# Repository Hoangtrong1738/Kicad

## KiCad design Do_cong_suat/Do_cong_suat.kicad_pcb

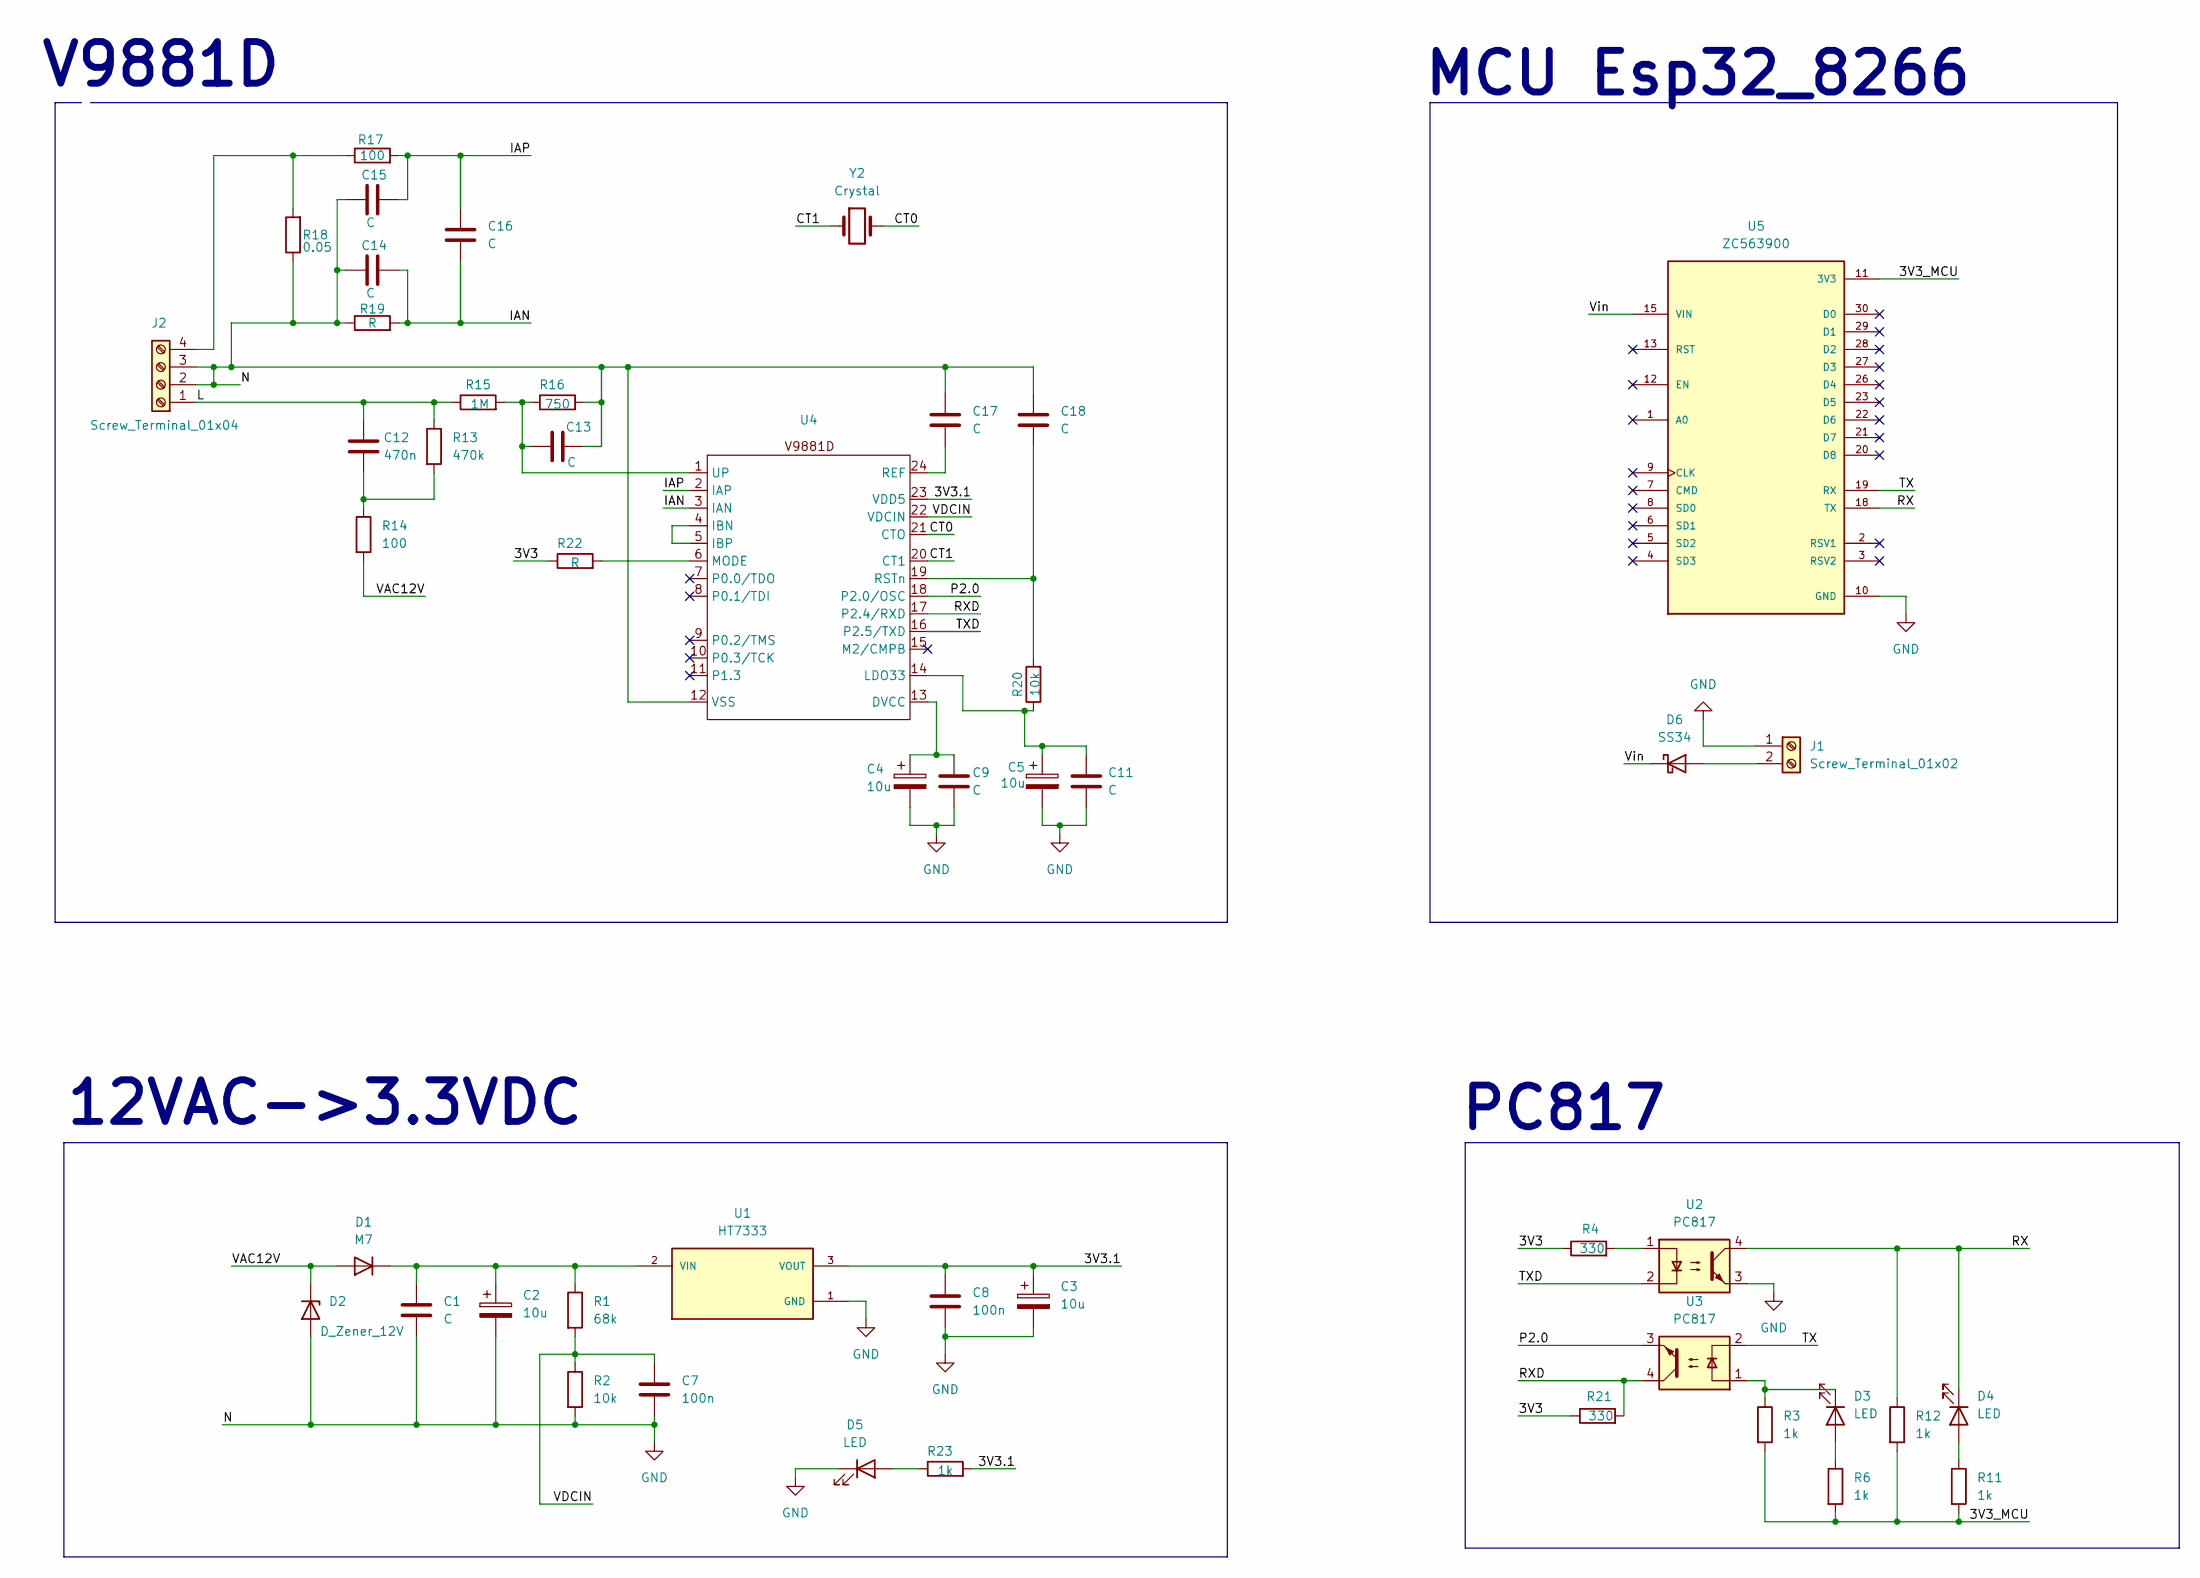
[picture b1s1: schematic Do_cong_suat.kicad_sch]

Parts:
C1, C9, C11, C13, C14, C15, C16, C17, C18: C; C_0805_2012Metric
C2: 10u; CP_Elec_5x5.4
C3, C4, C5: 10u; CP_EIA-3528-12_Kemet-T_HandSolder
C7, C8: 100n; C_0805_2012Metric
C12: 470n; C_Rect_L31.5mm_W15.0mm_P27.50mm_MKS4
D1: M7; D_SMA
D2: D_Zener_12V; D_SMA
D3, D4, D5: LED; LED_0805_2012Metric
D6: SS34; D_SMA
J1: Screw_Terminal_01x02; TerminalBlock_Phoenix_MKDS-1,5-2-5.08_1x02_P5.08mm_Horizont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
J2: Screw_Terminal_01x04; TerminalBlock_Phoenix_MKDS-1,5-4-5.08_1x04_P5.08mm_Horizont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
R1: 68k; R_0805_2012Metric
R2, R20: 10k; R_0805_2012Metric
R3, R6, R11, R12, R23: 1k; R_0805_2012Metric
R4, R21: 330; R_0805_2012Metric
R13: 470k; R_Axial_DIN0309_L9.0mm_D3.2mm_P15.24mm_Horizontal
R14, R17: 100; R_0805_2012Metric
R15: 1M; R_Axial_DIN0207_L6.3mm_D2.5mm_P10.16mm_Horizontal
R16: 750; R_0805_2012Metric
R18: 0.05; R_0805_2012Metric
R19, R22: R; R_0805_2012Metric
U1: HT7333; IC_HT7333; PARTREV 1.80
U2, U3: PC817; DIP-4_W7.62mm
U4: V9881D
U5: ZC563900; MODULE_ZC563900; PARTREV 1.0
Y2: Crystal; Crystal_AT310_D3.0mm_L10.0mm_Horizontal_1EP_style1

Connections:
/3V3.1: C3.1, C8.1, R23.2, U1.3 (VOUT), U4.23 (VDD5)
/CT0: U4.21 (CTO), Y2.2
/CT1: U4.20 (CT1), Y2.1
/IAN: C14.2, C16.2, R19.2, U4.3 (IAN)
/IAP: C15.2, C16.1, R17.2, U4.2 (IAP)
/L: C12.1, J2.1, R13.1, R15.1
/P2.0: U3.3, U4.18 (P2.0/OSC)
/RX: D4.1 (K), R12.1, U2.4, U5.18 (TX)
/RXD: R21.2, U3.4, U4.17 (P2.4/RXD)
/TX: U3.2, U5.19 (RX)
/TXD: U2.2, U4.16 (P2.5/TXD)
/VAC12V: D1.2 (A), D2.1 (K), R14.2
/VDCIN: C7.1, R1.2, R2.1, U4.22 (VDCIN)
/Vin: D6.1 (K), U5.15 (VIN)
GND: C1.2, C2.2, C3.2, C4.2, C5.2, C7.2, C8.2, C9.2, C11.2, C13.2, C14.1, C15.1, C17.1, C18.1, D2.2 (A), D5.1 (K), J1.1, J2.2, J2.3, R2.2, R16.2, R18.1, R19.1, U1.1 (GND), U2.3, U4.12 (VSS), U5.10 (GND), U5.14 (GND), U5.17 (GND), U5.24 (GND)
unnamed: C12.2, R13.2, R14.1
unnamed: C1.1, C2.1, D1.1 (K), R1.1, U1.2 (VIN)
unnamed: D3.2 (A), R6.1
unnamed: D3.1 (K), R3.1, U3.1
unnamed: D4.2 (A), R11.1
unnamed: D5.2 (A), R23.1
unnamed: D6.2 (A), J1.2
unnamed: J2.4, R17.1, R18.2
unnamed: R4.2, U2.1
unnamed: C4.1, C9.1, U4.13 (DVCC)
unnamed: U4.4 (IBN), U4.5 (IBP)
unnamed: C5.1, C11.1, R20.1, U4.14 (LDO33)
unnamed: R22.2, U4.6 (MODE)
unnamed: C17.2, U4.24 (REF)
unnamed: C18.2, R20.2, U4.19 (RSTn)
unnamed: C13.1, R15.2, R16.1, U4.1 (UP)

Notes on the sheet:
12VAC->3.3VDC
PC817
MCU Esp32_8266
V9881D

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
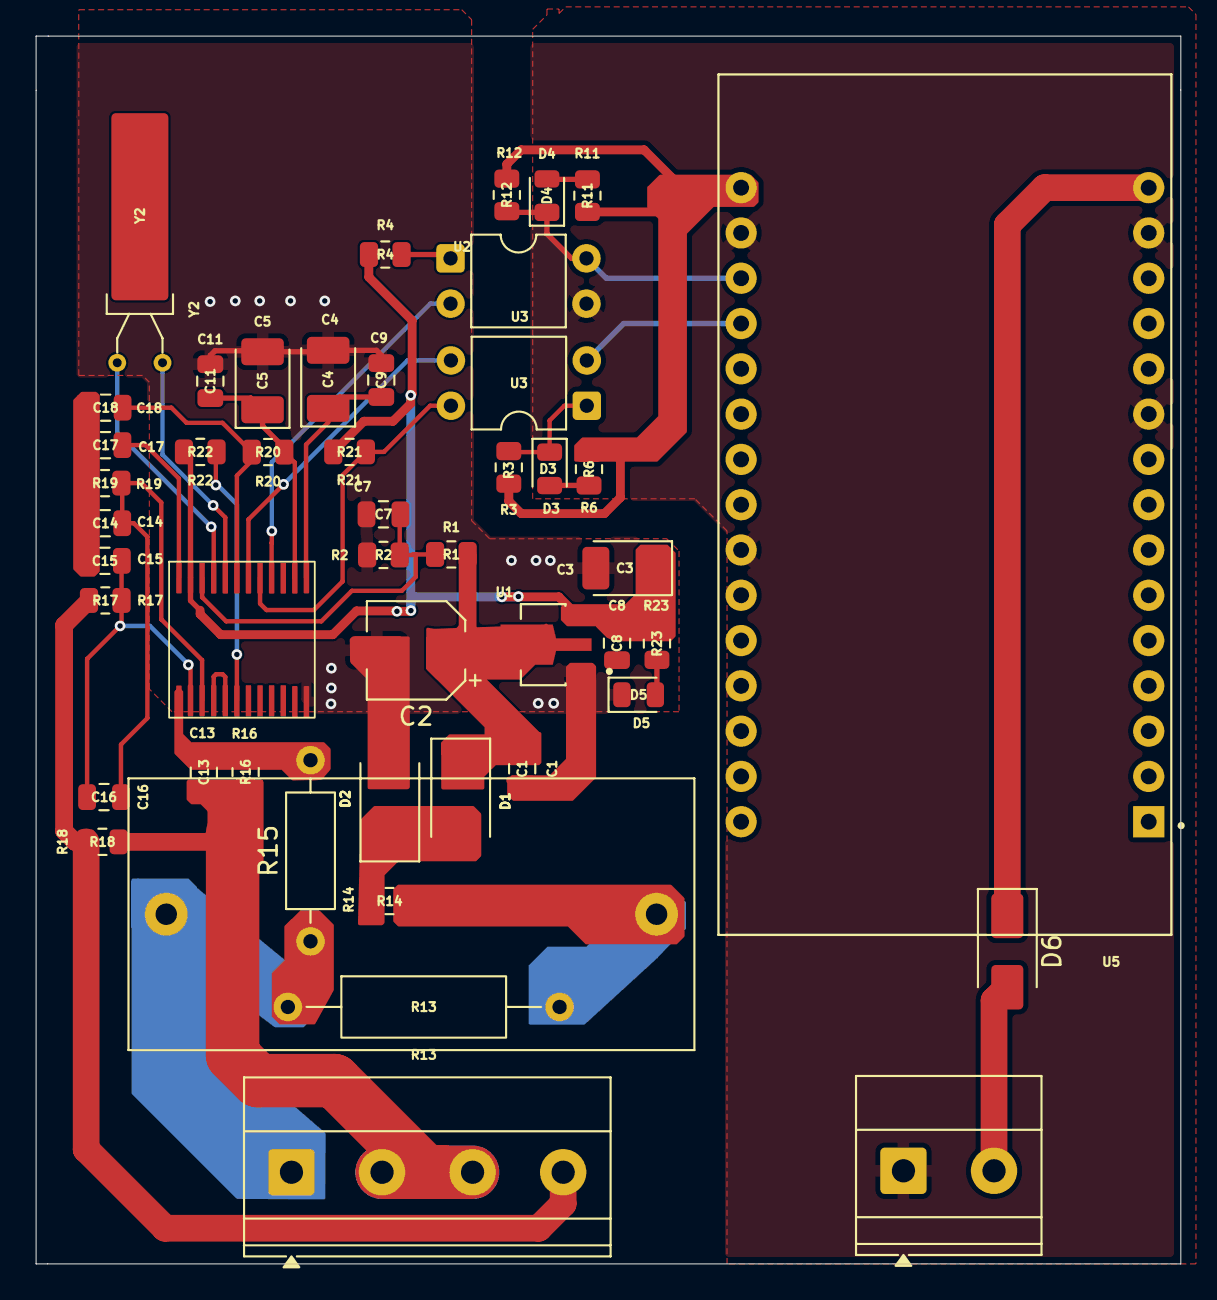
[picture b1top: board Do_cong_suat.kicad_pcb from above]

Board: 2 copper layers, 64.2 x 68.9 mm, 48 parts (0 on the bottom side), 32 nets.

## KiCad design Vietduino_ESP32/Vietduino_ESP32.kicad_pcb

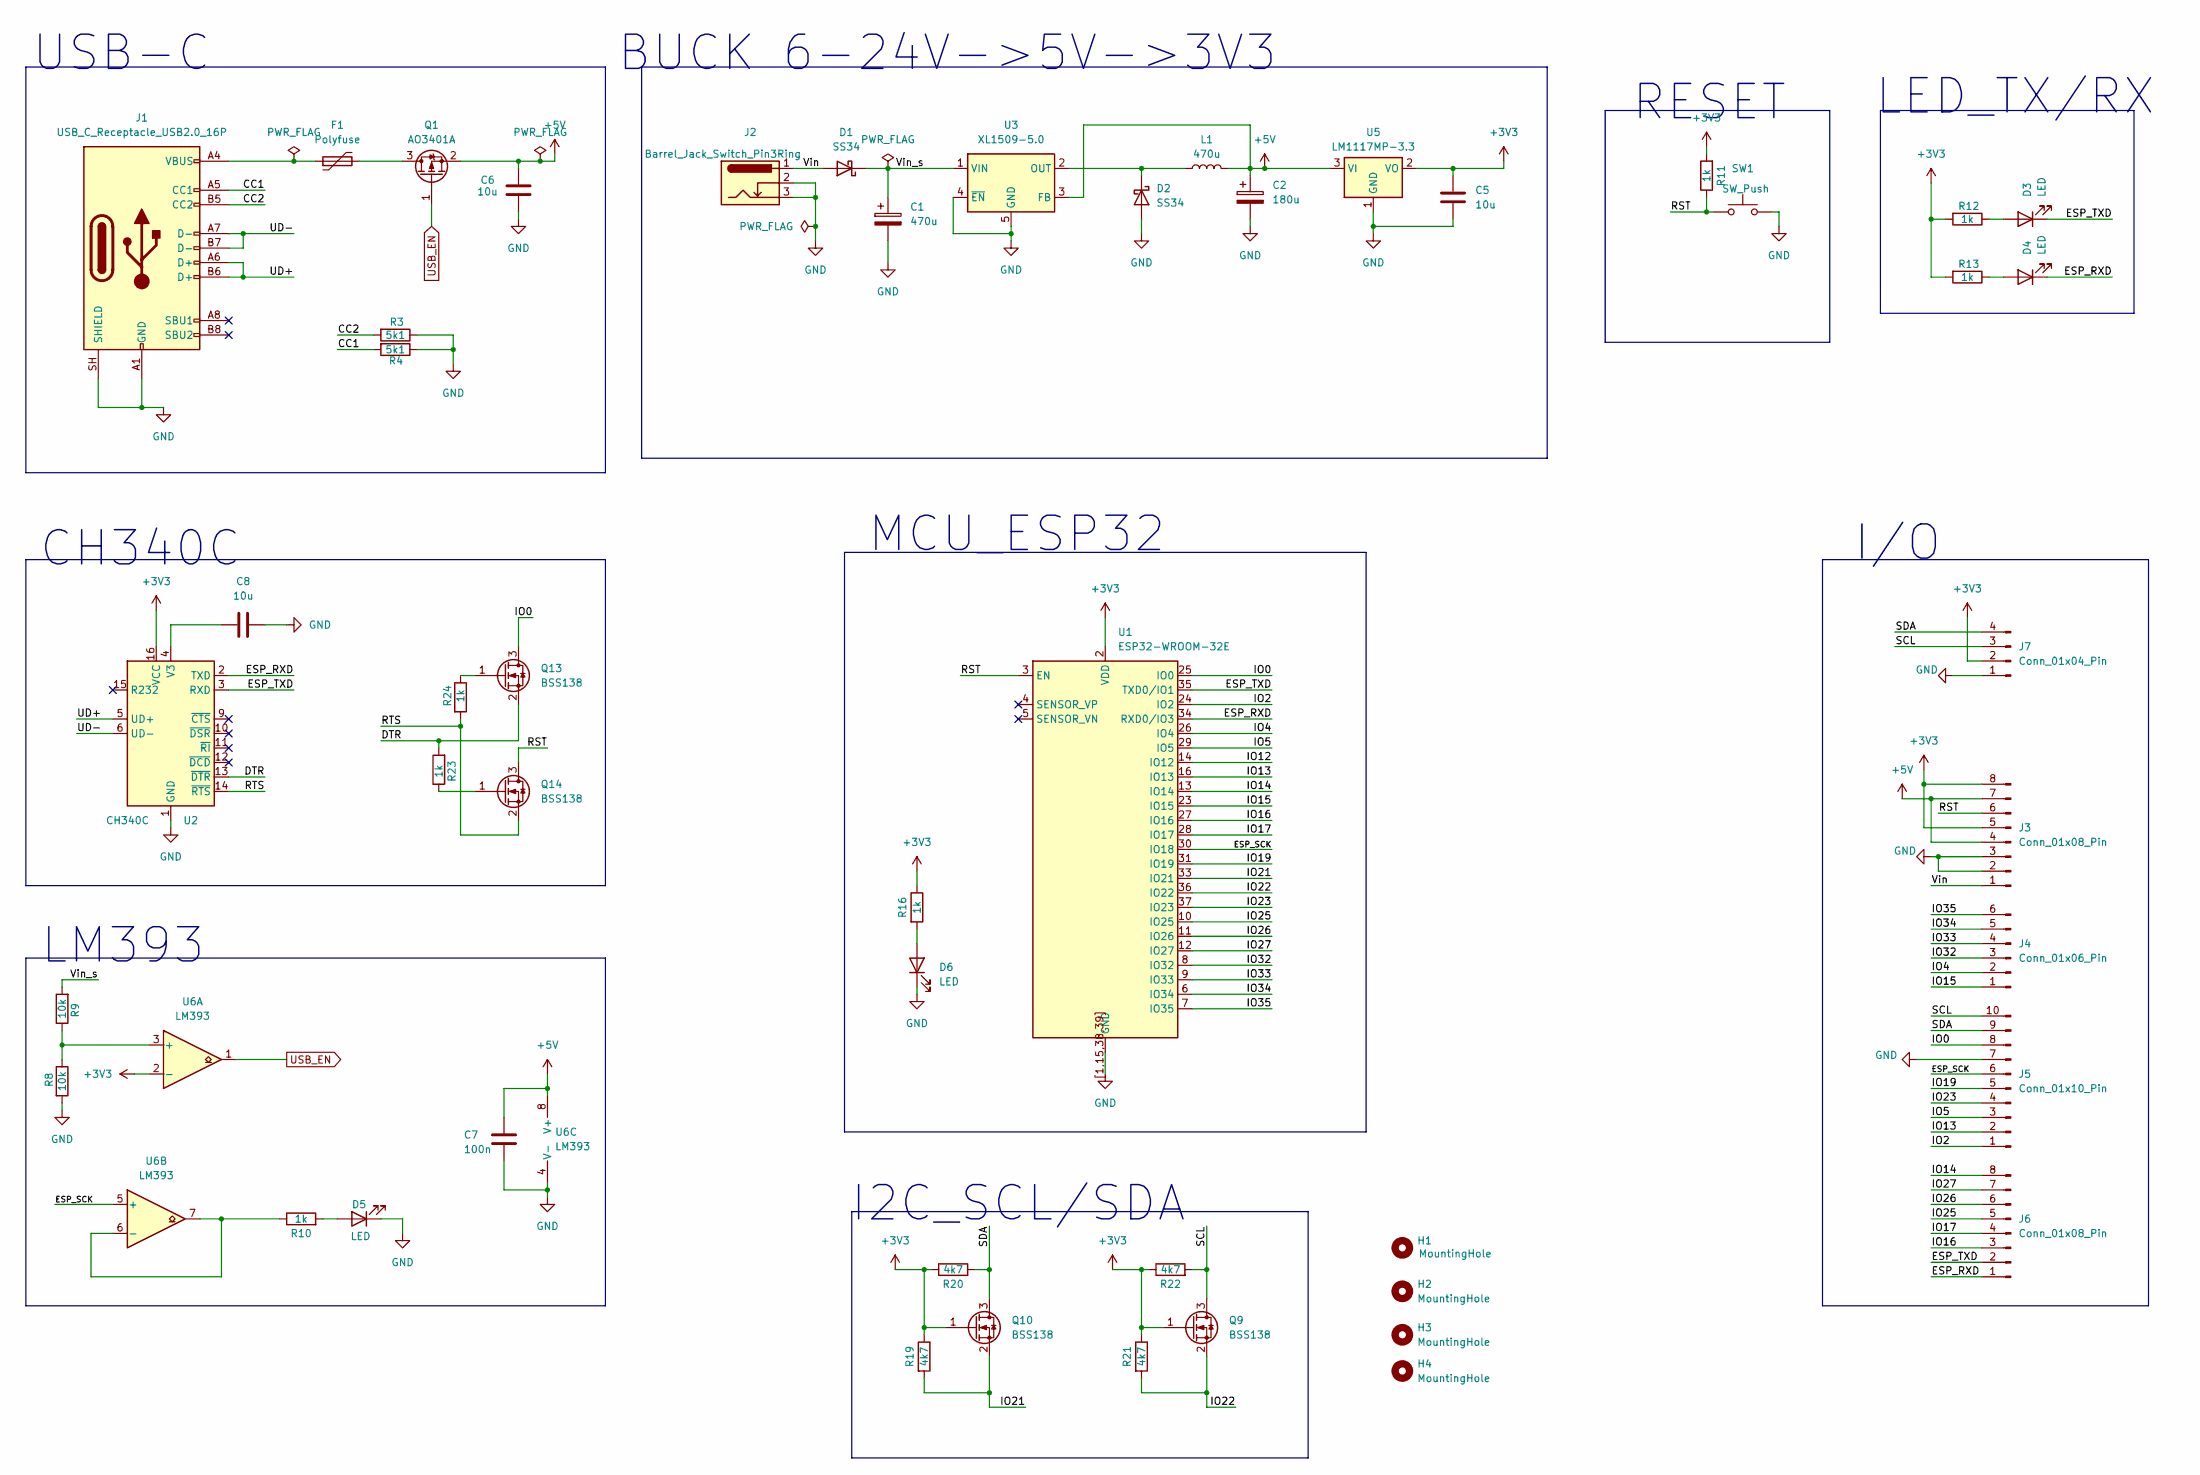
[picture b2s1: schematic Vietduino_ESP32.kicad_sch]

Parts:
C1: 470u; CP_Elec_6.3x5.4
C2: 180u; CP_Elec_6.3x5.4
C5, C6, C8: 10u; C_0805_2012Metric
C7: 100n; C_0805_2012Metric
D1, D2: SS34; D_SMA
D3, D4, D5, D6: LED; LED_0805_2012Metric
F1: Polyfuse; Fuse_0805_2012Metric
H1, H2, H3, H4: MountingHole; MountingHole_2.1mm
J1: USB_C_Receptacle_USB2.0_16P; USB_C_Receptacle_Palconn_UTC16-G
J2: Barrel_Jack_Switch_Pin3Ring; BarrelJack_Wuerth_6941xx301002
J3, J6: Conn_01x08_Pin; PinHeader_1x08_P2.54mm_Vertical
J4: Conn_01x06_Pin; PinHeader_1x06_P2.54mm_Vertical
J5: Conn_01x10_Pin; PinHeader_1x10_P2.54mm_Vertical
J7: Conn_01x04_Pin; PinSocket_1x04_P2.54mm_Vertical
L1: 470u; L_7.3x7.3_H4.5
Q1: AO3401A; SOT-23
Q9, Q10, Q13, Q14: BSS138; SOT-23
R3, R4: 5k1; R_0805_2012Metric
R8, R9: 10k; R_0805_2012Metric
R10, R11, R12, R13, R16, R23, R24: 1k; R_0805_2012Metric
R19, R20, R21, R22: 4k7; R_0805_2012Metric
SW1: SW_Push; SW_Push_1P1T_NO_CK_KMR2
U1: ESP32-WROOM-32E
U2: CH340C; SOIC-16_3.9x9.9mm_P1.27mm
U3: XL1509-5.0; SOIC-8_3.9x4.9mm_P1.27mm
U5: LM1117MP-3.3; SOT-223-3_TabPin2
U6: LM393; SOIC-8_3.9x4.9mm_P1.27mm

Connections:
+3V3: C5.1, J3.5, J3.8, J7.2, Q9.1 (G), Q10.1 (G), R11.2, R12.2, R13.2, R16.1, R19.1, R20.1, R21.1, R22.1, U1.2 (VDD), U2.16 (VCC), U5.2 (VO), U6.2 (-)
+5V: C2.1, C6.2, C7.1, J3.4, J3.7, L1.2, Q1.2 (S), U3.3 (FB), U5.3 (VI), U6.8 (V+)
/CC1: J1.A5 (CC1), R4.2
/CC2: J1.B5 (CC2), R3.2
/DTR: Q13.2 (S), R23.2, U2.13 (~DTR)
/ESP_RXD: D4.1 (K), J6.1, U1.34 (RXD0/IO3), U2.2 (TXD)
/ESP_SCK: J5.6, U1.30 (IO18), U6.5 (+)
/ESP_TXD: D3.1 (K), J6.2, U1.35 (TXD0/IO1), U2.3 (RXD)
/IO0: J5.8, Q13.3 (D), U1.25 (IO0)
/IO2: J5.1, U1.24 (IO2)
/IO4: J4.2, U1.26 (IO4)
/IO5: J5.3, U1.29 (IO5)
/IO12: U1.14 (IO12)
/IO13: J5.2, U1.16 (IO13)
/IO14: J6.8, U1.13 (IO14)
/IO15: J4.1, U1.23 (IO15)
/IO16: J6.3, U1.27 (IO16)
/IO17: J6.4, U1.28 (IO17)
/IO19: J5.5, U1.31 (IO19)
/IO21: Q10.2 (S), R19.2, U1.33 (IO21)
/IO22: Q9.2 (S), R21.2, U1.36 (IO22)
/IO23: J5.4, U1.37 (IO23)
/IO25: J6.5, U1.10 (IO25)
/IO26: J6.6, U1.11 (IO26)
/IO27: J6.7, U1.12 (IO27)
/IO32: J4.3, U1.8 (IO32)
/IO33: J4.4, U1.9 (IO33)
/IO34: J4.5, U1.6 (IO34)
/IO35: J4.6, U1.7 (IO35)
/RST: J3.6, Q14.3 (D), R11.1, SW1.1, U1.3 (EN)
/RTS: Q14.2 (S), R24.2, U2.14 (~RTS)
/SCL: J5.10, J7.3, Q9.3 (D), R22.2
/SDA: J5.9, J7.4, Q10.3 (D), R20.2
/UD+: J1.A6 (D+), J1.B6 (D+), U2.5 (UD+)
/UD-: J1.A7 (D-), J1.B7 (D-), U2.6 (UD-)
/Vin: D1.2 (A), J2.1, J3.1
/Vin_s: C1.1, D1.1 (K), R9.2, U3.1 (VIN)
GND: C1.2, C2.2, C5.2, C6.1, C7.2, C8.2, D2.2 (A), D5.1 (K), D6.1 (K), J1.A1 (GND), J1.A12 (GND), J1.B1 (GND), J1.B12 (GND), J1.SH (SHIELD), J2.2, J2.3, J3.2, J3.3, J5.7, J7.1, R3.1, R4.1, R8.2, SW1.2, U1.1 (GND), U1.15 (GND), U1.38 (GND), U1.39 (GND), U1.[1,15,38,39] (GND), U2.1 (GND), U3.4 (~EN), U3.5 (GND), U3.6 (GND), U3.7 (GND), U3.8 (GND), U5.1 (GND), U6.4 (V-)
unnamed: D2.1 (K), L1.1, U3.2 (OUT)
unnamed: D3.2 (A), R12.1
unnamed: D4.2 (A), R13.1
unnamed: D5.2 (A), R10.2
unnamed: D6.2 (A), R16.2
unnamed: F1.1, J1.A4 (VBUS), J1.A9 (VBUS), J1.B4 (VBUS), J1.B9 (VBUS)
unnamed: F1.2, Q1.3 (D)
unnamed: Q13.1 (G), R24.1
unnamed: Q14.1 (G), R23.1
unnamed: C8.1, U2.4 (V3)
unnamed: R8.1, R9.1, U6.3 (+)
unnamed: R10.1, U6.6 (-), U6.7
USB_EN: Q1.1 (G), U6.1

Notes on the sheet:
LED_TX/RX
I2C_SCL/SDA
CH340C
I/O
MCU_ESP32
LM393
BUCK 6-24V->5V->3V3
USB-C
RESET

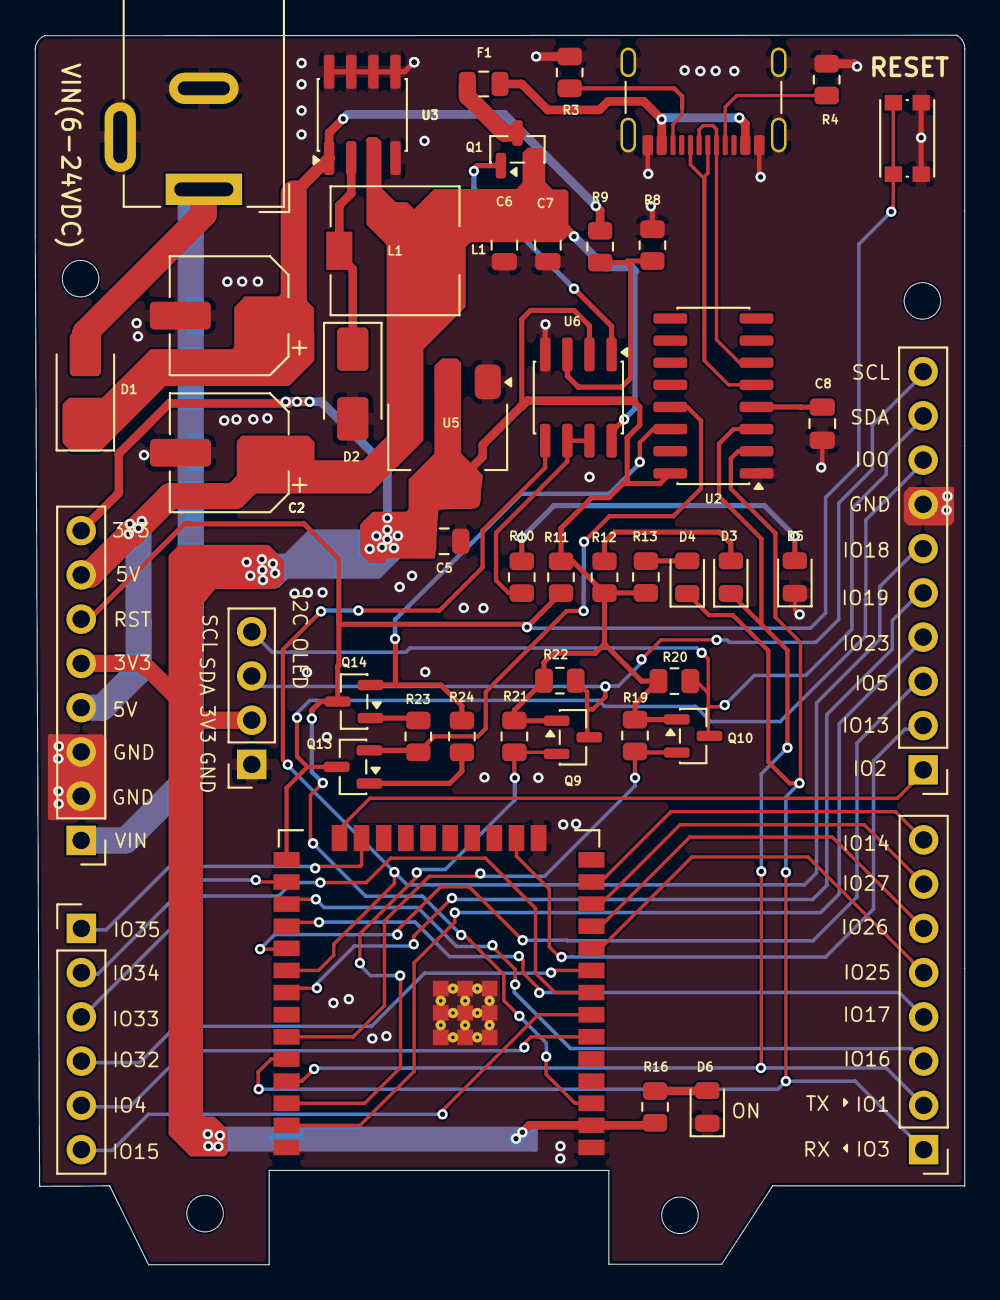
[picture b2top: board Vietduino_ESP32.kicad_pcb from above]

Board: 2 copper layers, 53.3 x 70.6 mm, 51 parts (0 on the bottom side), 50 nets.

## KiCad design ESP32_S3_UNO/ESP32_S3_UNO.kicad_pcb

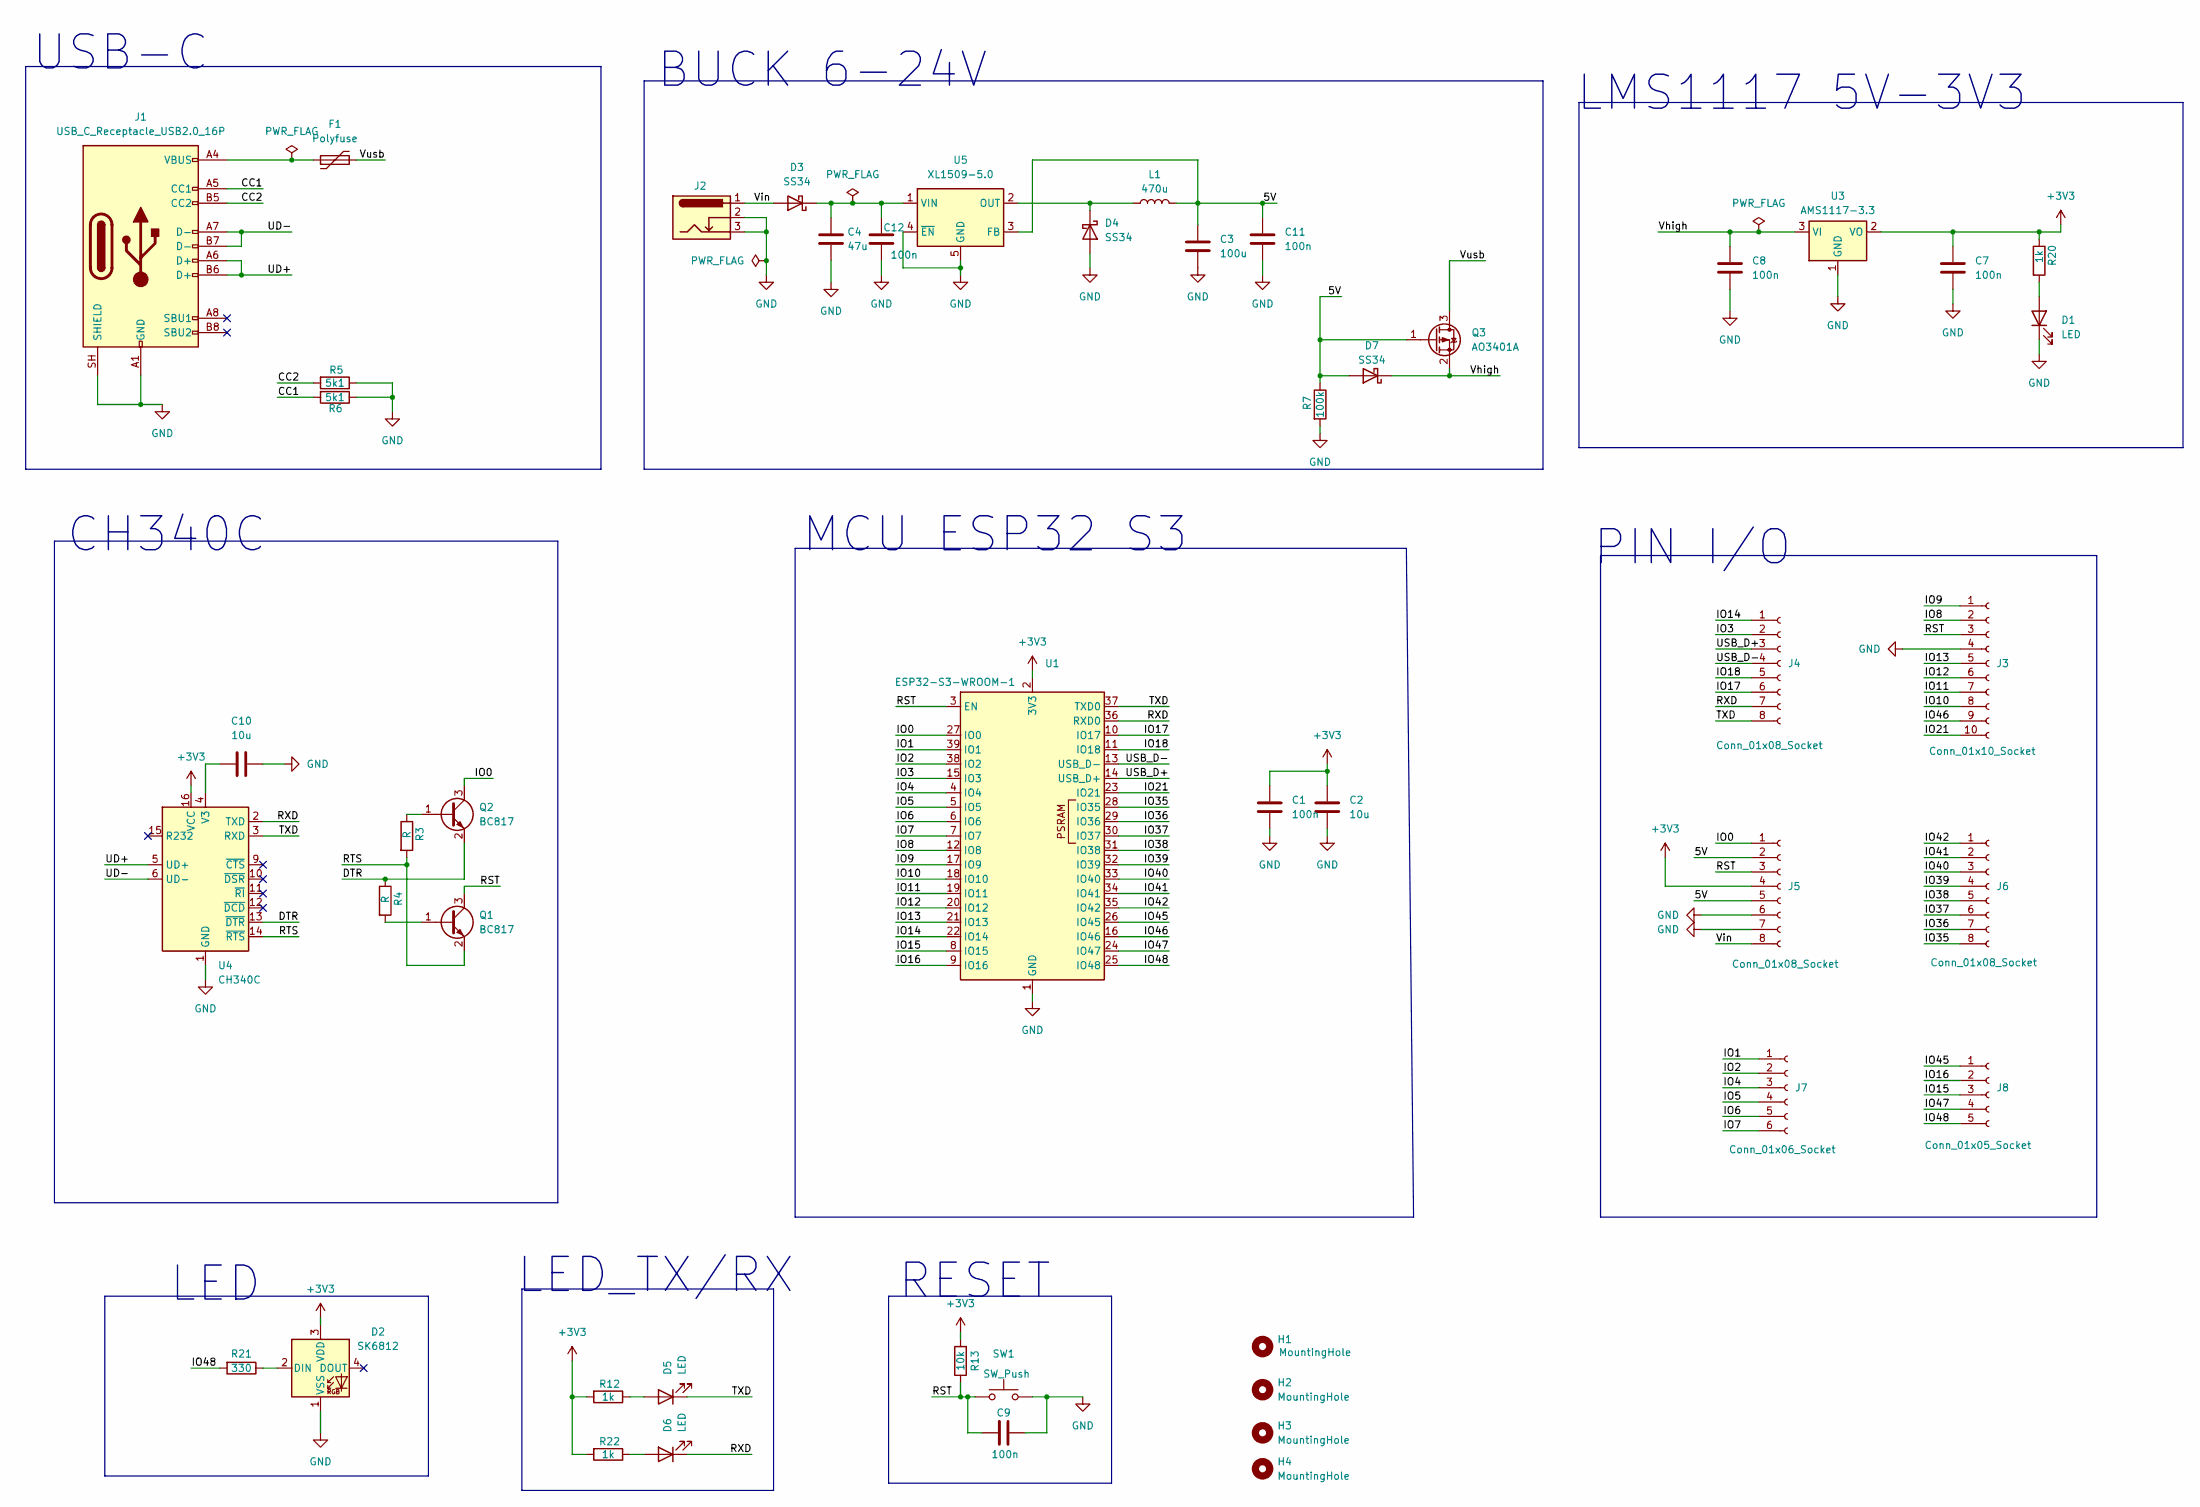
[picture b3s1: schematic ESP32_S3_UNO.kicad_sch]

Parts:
C1, C7, C8, C9, C11, C12: 100n; C_0805_2012Metric
C2, C10: 10u; C_0805_2012Metric
C3: 100u; C_1210_3225Metric
C4: 47u; C_1210_3225Metric
D1, D5, D6: LED; LED_0805_2012Metric
D2: SK6812; LED_SK6812_PLCC4_5.0x5.0mm_P3.2mm
D3, D4, D7: SS34; D_SMA
F1: Polyfuse; Fuse_0805_2012Metric
H1, H2, H3, H4: MountingHole; MountingHole_2.1mm
J1: USB_C_Receptacle_USB2.0_16P; USB_C_Receptacle_Palconn_UTC16-G
J2: Barrel_Jack_Switch_Pin3Ring; BarrelJack_Wuerth_6941xx301002
J3: Conn_01x10_Socket; PinSocket_1x10_P2.54mm_Vertical
J4, J5, J6: Conn_01x08_Socket; PinSocket_1x08_P2.54mm_Vertical
J7: Conn_01x06_Socket; PinSocket_1x06_P2.54mm_Vertical
J8: Conn_01x05_Socket; PinSocket_1x05_P2.54mm_Vertical
L1: 470u; L_7.3x7.3_H4.5
Q1, Q2: BC817; SOT-23
Q3: AO3401A; SOT-23
R3, R4: R; R_0805_2012Metric
R5, R6: 5k1; R_0805_2012Metric
R7: 100k; R_0805_2012Metric
R12, R20, R22: 1k; R_0805_2012Metric
R13: 10k; R_0805_2012Metric
R21: 330; R_0805_2012Metric
SW1: SW_Push; SW_Push_1P1T_NO_CK_KMR2
U1: ESP32-S3-WROOM-1
U3: AMS1117-3.3; SOT-223-3_TabPin2
U4: CH340C; SOIC-16_3.9x9.9mm_P1.27mm
U5: XL1509-5.0; SOIC-8_3.9x4.9mm_P1.27mm

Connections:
+3V3: C1.1, C2.1, C7.1, D2.3 (VDD), J5.4, R12.2, R13.2, R20.1, R22.2, U1.2 (3V3), U3.2 (VO), U4.16 (VCC)
/5V: C3.1, C11.1, D7.2 (A), J5.2, J5.5, L1.2, Q3.1 (G), R7.1, U5.3 (FB)
/CC1: J1.A5 (CC1), R6.2
/CC2: J1.B5 (CC2), R5.2
/DTR: Q2.2 (E), R4.1, U4.13 (~DTR)
/IO0: J5.1, Q2.3 (C), U1.27 (IO0)
/IO1: J7.1, U1.39 (IO1)
/IO2: J7.2, U1.38 (IO2)
/IO3: J4.2, U1.15 (IO3)
/IO4: J7.3, U1.4 (IO4)
/IO5: J7.4, U1.5 (IO5)
/IO6: J7.5, U1.6 (IO6)
/IO7: J7.6, U1.7 (IO7)
/IO8: J3.2, U1.12 (IO8)
/IO9: J3.1, U1.17 (IO9)
/IO10: J3.8, U1.18 (IO10)
/IO11: J3.7, U1.19 (IO11)
/IO12: J3.6, U1.20 (IO12)
/IO13: J3.5, U1.21 (IO13)
/IO14: J4.1, U1.22 (IO14)
/IO15: J8.3, U1.8 (IO15)
/IO16: J8.2, U1.9 (IO16)
/IO17: J4.6, U1.10 (IO17)
/IO18: J4.5, U1.11 (IO18)
/IO21: J3.10, U1.23 (IO21)
/IO35: J6.8, U1.28 (IO35)
/IO36: J6.7, U1.29 (IO36)
/IO37: J6.6, U1.30 (IO37)
/IO38: J6.5, U1.31 (IO38)
/IO39: J6.4, U1.32 (IO39)
/IO40: J6.3, U1.33 (IO40)
/IO41: J6.2, U1.34 (IO41)
/IO42: J6.1, U1.35 (IO42)
/IO45: J8.1, U1.26 (IO45)
/IO46: J3.9, U1.16 (IO46)
/IO47: J8.4, U1.24 (IO47)
/IO48: J8.5, R21.2, U1.25 (IO48)
/RST: C9.1, J3.3, J5.3, Q1.3 (C), R13.1, SW1.1, U1.3 (EN)
/RTS: Q1.2 (E), R3.2, U4.14 (~RTS)
/RXD: D6.1 (K), J4.7, U1.36 (RXD0), U4.2 (TXD)
/TXD: D5.1 (K), J4.8, U1.37 (TXD0), U4.3 (RXD)
/UD+: J1.A6 (D+), J1.B6 (D+), U4.5 (UD+)
/UD-: J1.A7 (D-), J1.B7 (D-), U4.6 (UD-)
/USB_D+: J4.3, U1.14 (USB_D+)
/USB_D-: J4.4, U1.13 (USB_D-)
/Vhigh: C8.1, D7.1 (K), Q3.2 (S), U3.3 (VI)
/Vin: D3.2 (A), J2.1, J5.8
/Vusb: F1.2, Q3.3 (D)
GND: C1.2, C2.2, C3.2, C4.2, C7.2, C8.2, C9.2, C10.2, C11.2, C12.2, D1.1 (K), D2.1 (VSS), D4.2 (A), J1.A1 (GND), J1.A12 (GND), J1.B1 (GND), J1.B12 (GND), J1.SH (SHIELD), J2.2, J2.3, J3.4, J5.6, J5.7, R5.1, R6.1, R7.2, SW1.2, U1.1 (GND), U1.40 (GND), U1.41 (GND), U3.1 (GND), U4.1 (GND), U5.4 (~EN), U5.5 (GND), U5.6 (GND), U5.7 (GND), U5.8 (GND)
unnamed: D1.2 (A), R20.2
unnamed: D2.2 (DIN), R21.1
unnamed: C4.1, C12.1, D3.1 (K), U5.1 (VIN)
unnamed: D4.1 (K), L1.1, U5.2 (OUT)
unnamed: D5.2 (A), R12.1
unnamed: D6.2 (A), R22.1
unnamed: F1.1, J1.A4 (VBUS), J1.A9 (VBUS), J1.B4 (VBUS), J1.B9 (VBUS)
unnamed: Q1.1 (B), R4.2
unnamed: Q2.1 (B), R3.1
unnamed: C10.1, U4.4 (V3)

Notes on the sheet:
BUCK 6-24V
LMS1117 5V-3V3
LED_TX/RX
LED
USB-C
MCU ESP32 S3
CH340C
PIN I/O
RESET

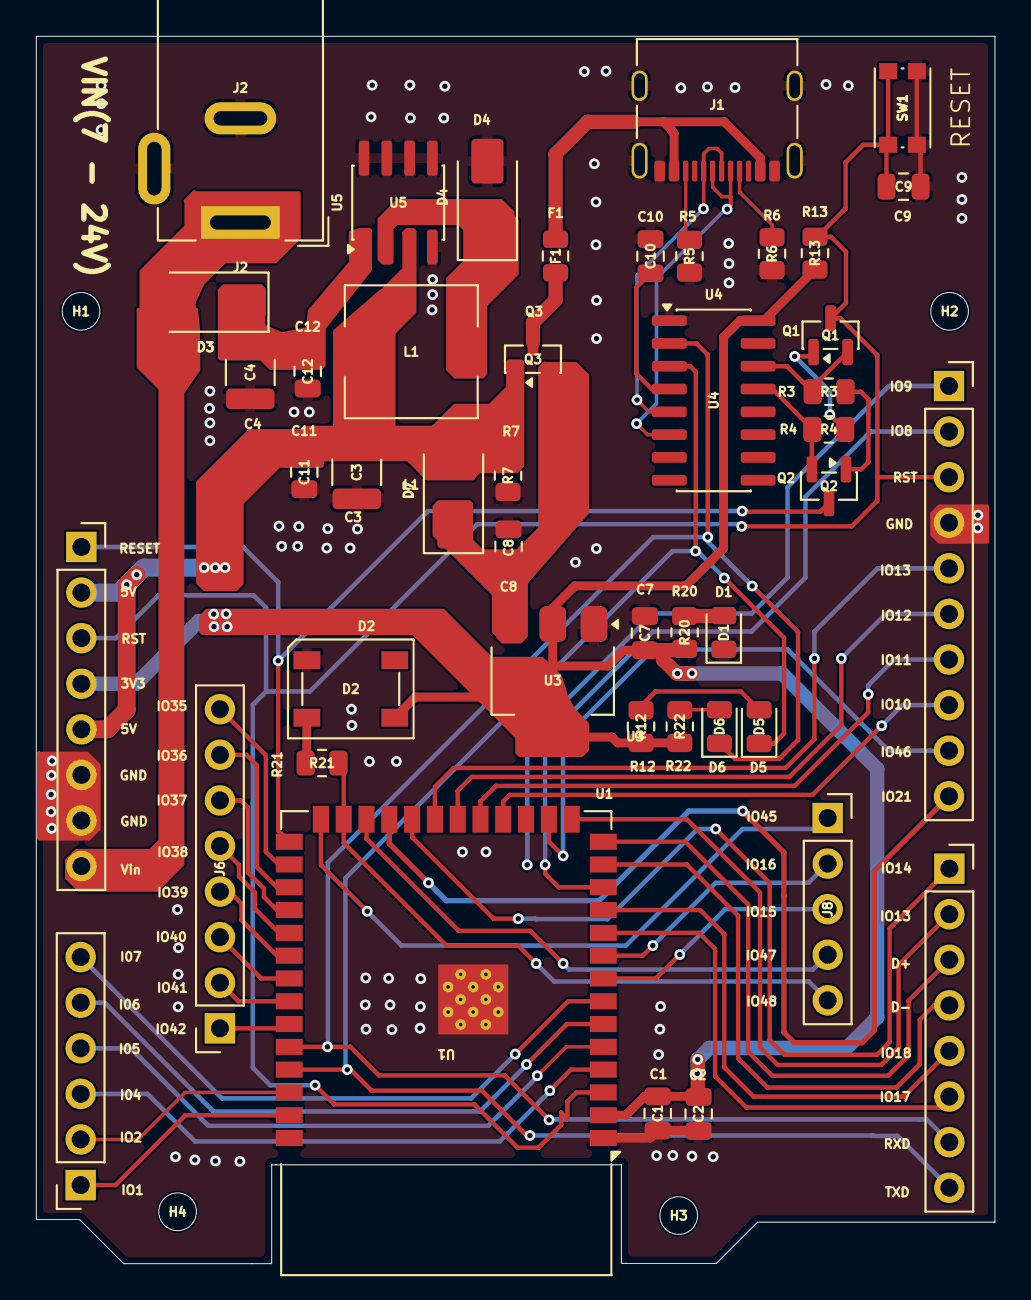
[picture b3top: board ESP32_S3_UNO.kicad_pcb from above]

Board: 2 copper layers, 53.4 x 68.4 mm, 49 parts (0 on the bottom side), 59 nets.

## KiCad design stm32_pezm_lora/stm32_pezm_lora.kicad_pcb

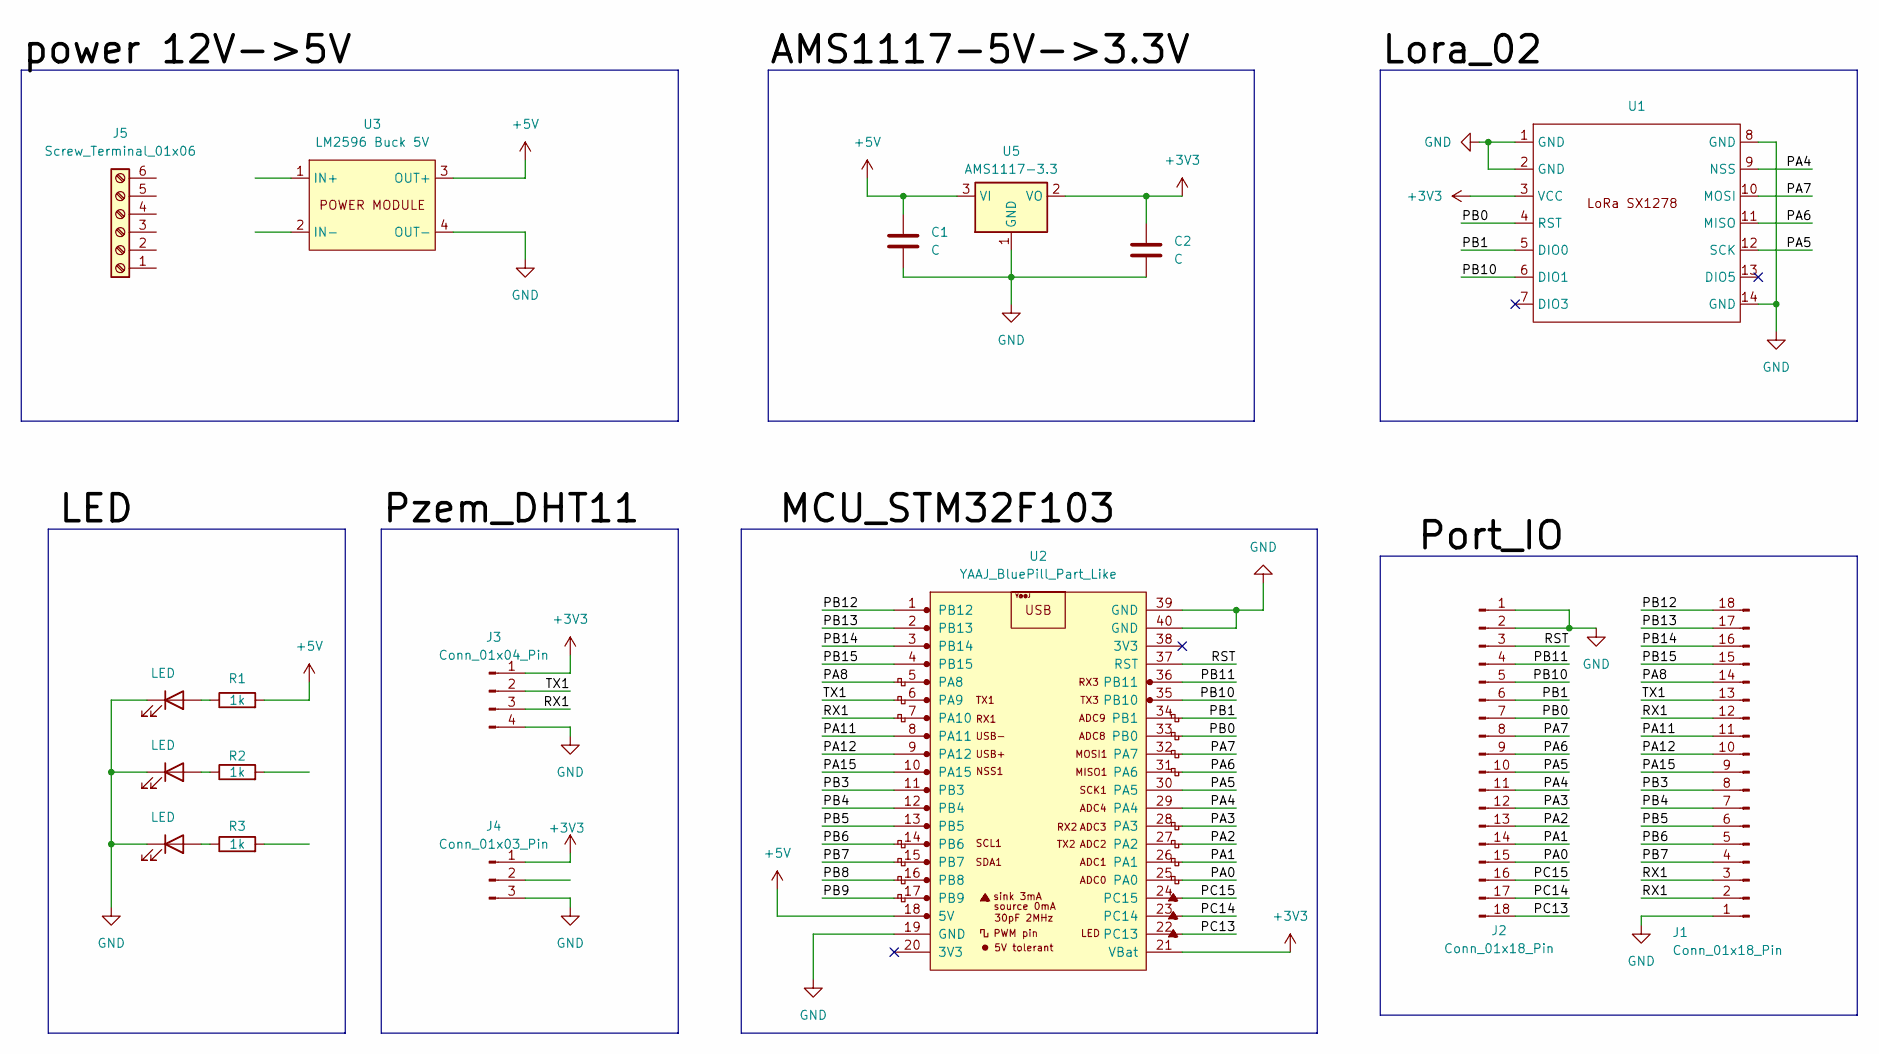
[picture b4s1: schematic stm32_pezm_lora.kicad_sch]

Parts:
C1, C2: C; C_0805_2012Metric
D2, D3, D4: LED; LED_D5.0mm
J1, J2: Conn_01x18_Pin; PinHeader_1x18_P2.54mm_Vertical
J3: Conn_01x04_Pin; JST_XH_B4B-XH-A_1x04_P2.50mm_Vertical
J4: Conn_01x03_Pin; JST_XH_B3B-XH-A_1x03_P2.50mm_Vertical
J5: Screw_Terminal_01x06; TerminalBlock_Phoenix_MKDS-1,5-6-5.08_1x06_P5.08mm_Horizont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
R1, R2, R3: 1k; R_1206_3216Metric
U1: LoRa_SX1278
U2: YAAJ_BluePill_Part_Like; YAAJ_BluePill_1
U3: LM2596 Buck 5V; MODULE_4P_45x22
U5: AMS1117-3.3; SOT-223-3_TabPin2

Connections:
+3V3: C2.1, J3.1, J4.1, U1.3 (VCC), U2.21 (VBat), U5.2 (VO)
+5V: C1.1, R1.2, U2.18 (5V), U3.3 (OUT+), U5.3 (VI)
/PA0: J2.15, U2.25 (PA0)
/PA1: J2.14, U2.26 (PA1)
/PA2: J2.13, U2.27 (PA2)
/PA3: J2.12, U2.28 (PA3)
/PA4: J2.11, U1.9 (NSS), U2.29 (PA4)
/PA5: J2.10, U1.12 (SCK), U2.30 (PA5)
/PA6: J2.9, U1.11 (MISO), U2.31 (PA6)
/PA7: J2.8, U1.10 (MOSI), U2.32 (PA7)
/PA8: J1.14, U2.5 (PA8)
/PA11: J1.11, U2.8 (PA11)
/PA12: J1.10, U2.9 (PA12)
/PA15: J1.9, U2.10 (PA15)
/PB0: J2.7, U1.4 (RST), U2.33 (PB0)
/PB1: J2.6, U1.5 (DIO0), U2.34 (PB1)
/PB3: J1.8, U2.11 (PB3)
/PB4: J1.7, U2.12 (PB4)
/PB5: J1.6, U2.13 (PB5)
/PB6: J1.5, U2.14 (PB6)
/PB7: J1.4, U2.15 (PB7)
/PB8: U2.16 (PB8)
/PB9: U2.17 (PB9)
/PB10: J2.5, U1.6 (DIO1), U2.35 (PB10)
/PB11: J2.4, U2.36 (PB11)
/PB12: J1.18, U2.1 (PB12)
/PB13: J1.17, U2.2 (PB13)
/PB14: J1.16, U2.3 (PB14)
/PB15: J1.15, U2.4 (PB15)
/PC13: J2.18, U2.22 (PC13)
/PC14: J2.17, U2.23 (PC14)
/PC15: J2.16, U2.24 (PC15)
/RST: J2.3, U2.37 (RST)
/RX1: J1.2, J1.3, J1.12, J3.3, U2.7 (PA10)
/TX1: J1.13, J3.2, U2.6 (PA9)
GND: C1.2, C2.2, D2.1 (K), D3.1 (K), D4.1 (K), J1.1, J2.1, J2.2, J3.4, J4.3, U1.1 (GND), U1.2 (GND), U1.8 (GND), U1.14 (GND), U2.19 (GND), U2.39 (GND), U2.40 (GND), U3.4 (OUT-), U5.1 (GND)
unnamed: D2.2 (A), R2.1
unnamed: D3.2 (A), R3.1
unnamed: D4.2 (A), R1.1

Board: 2 copper layers, 17 parts (0 on the bottom side), 37 nets, no tracks yet.
